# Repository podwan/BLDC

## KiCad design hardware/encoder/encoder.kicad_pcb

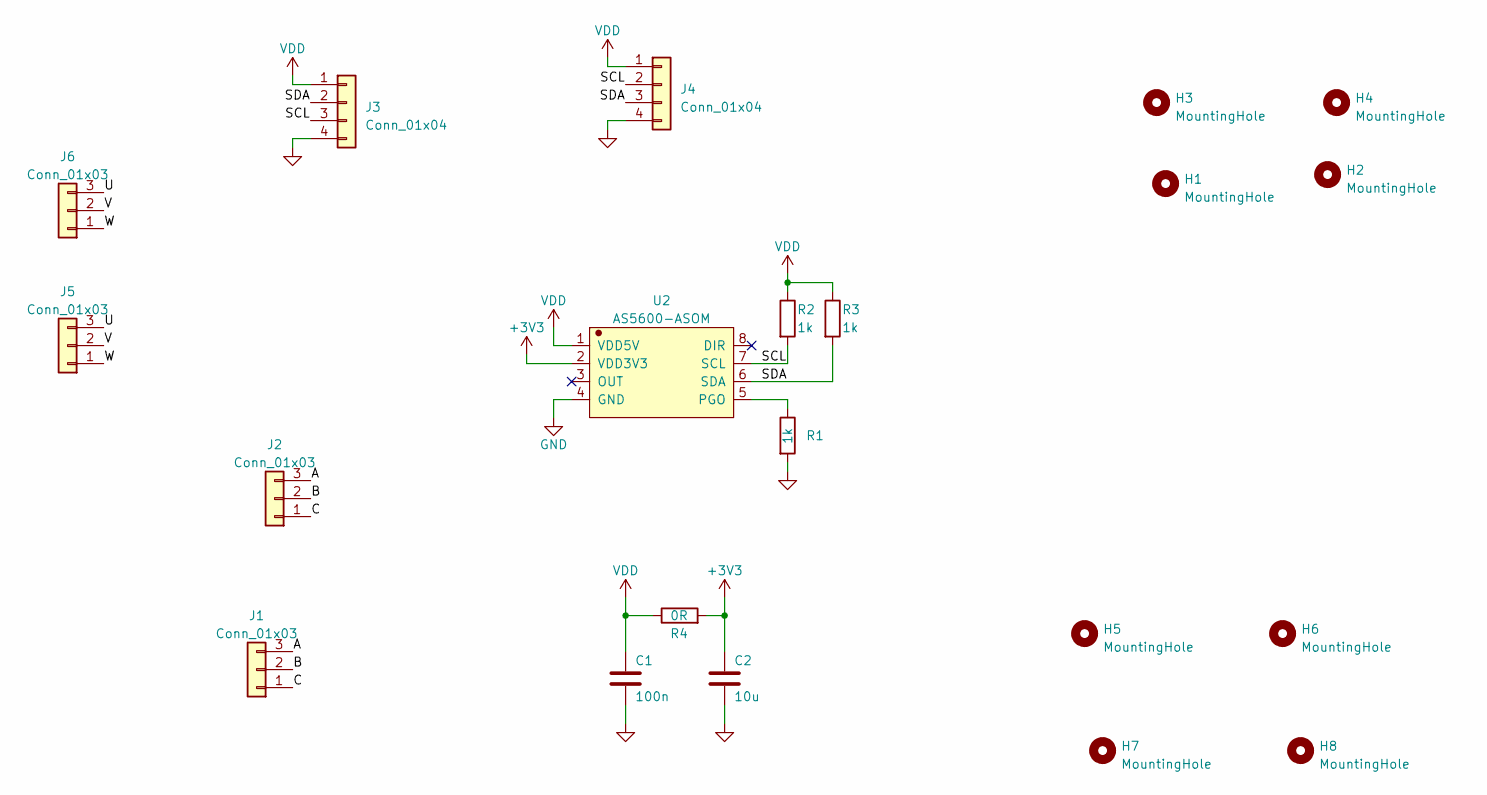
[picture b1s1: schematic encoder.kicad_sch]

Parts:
C1: 100n; C_0603_1608Metric_Pad1.08x0.95mm_HandSolder
C2: 10u; C_0805_2012Metric_Pad1.18x1.45mm_HandSolder
H1, H2, H3, H4: MountingHole; MountingHole_2.5mm_Pad_TopBottom
H5, H6, H7, H8: MountingHole; MountingHole_3mm_Pad_TopBottom
J1, J2: Conn_01x03; PinSocket_1x03_P2.54mm_Vertical
J3: Conn_01x04; PinSocket_1x04_P2.54mm_Vertical
J4: Conn_01x04; CONN-SMD_AFC10-S04QCA-00
J5, J6: Conn_01x03; CONN-SMD_AFC10-S03QCA-00
R1, R2, R3: 1k; C_0603_1608Metric_Pad1.08x0.95mm_HandSolder
R4: 0R; C_0603_1608Metric_Pad1.08x0.95mm_HandSolder
U2: AS5600-ASOM; SOIC-8_L5.0-W4.0-P1.27-LS6.0-BL

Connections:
+3V3: C2.1, R4.2, U2.2 (VDD3V3)
/A: J1.3, J2.3
/B: J1.2, J2.2
/C: J1.1, J2.1
/SCL: J3.3, J4.2, R2.2, U2.7 (SCL)
/SDA: J3.2, J4.3, R3.2, U2.6 (SDA)
/U: J5.3, J6.3
/V: J5.2, J6.2
/W: J5.1, J6.1
GND: C1.2, C2.2, J3.4, J4.4, R1.2, U2.4 (GND)
unnamed: R1.1, U2.5 (PGO)
VDD: C1.1, J3.1, J4.1, R2.1, R3.1, R4.1, U2.1 (VDD5V)

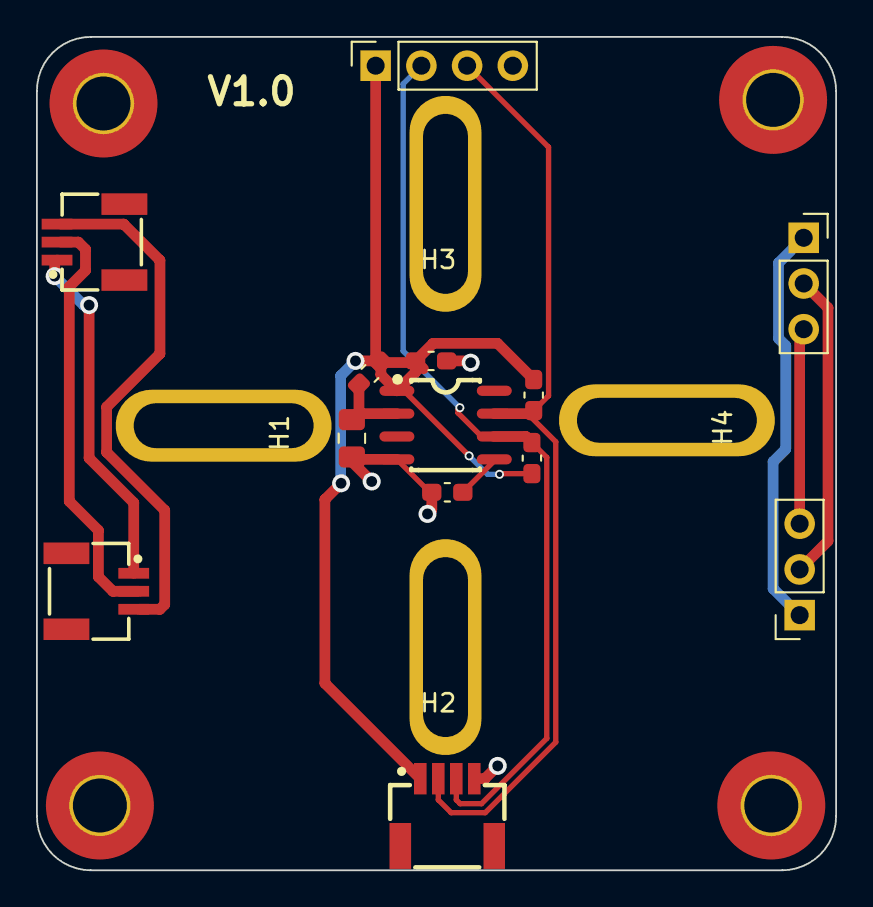
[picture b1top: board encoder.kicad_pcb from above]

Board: 2 copper layers, 44.4 x 46.3 mm, 21 parts (0 on the bottom side), 12 nets.

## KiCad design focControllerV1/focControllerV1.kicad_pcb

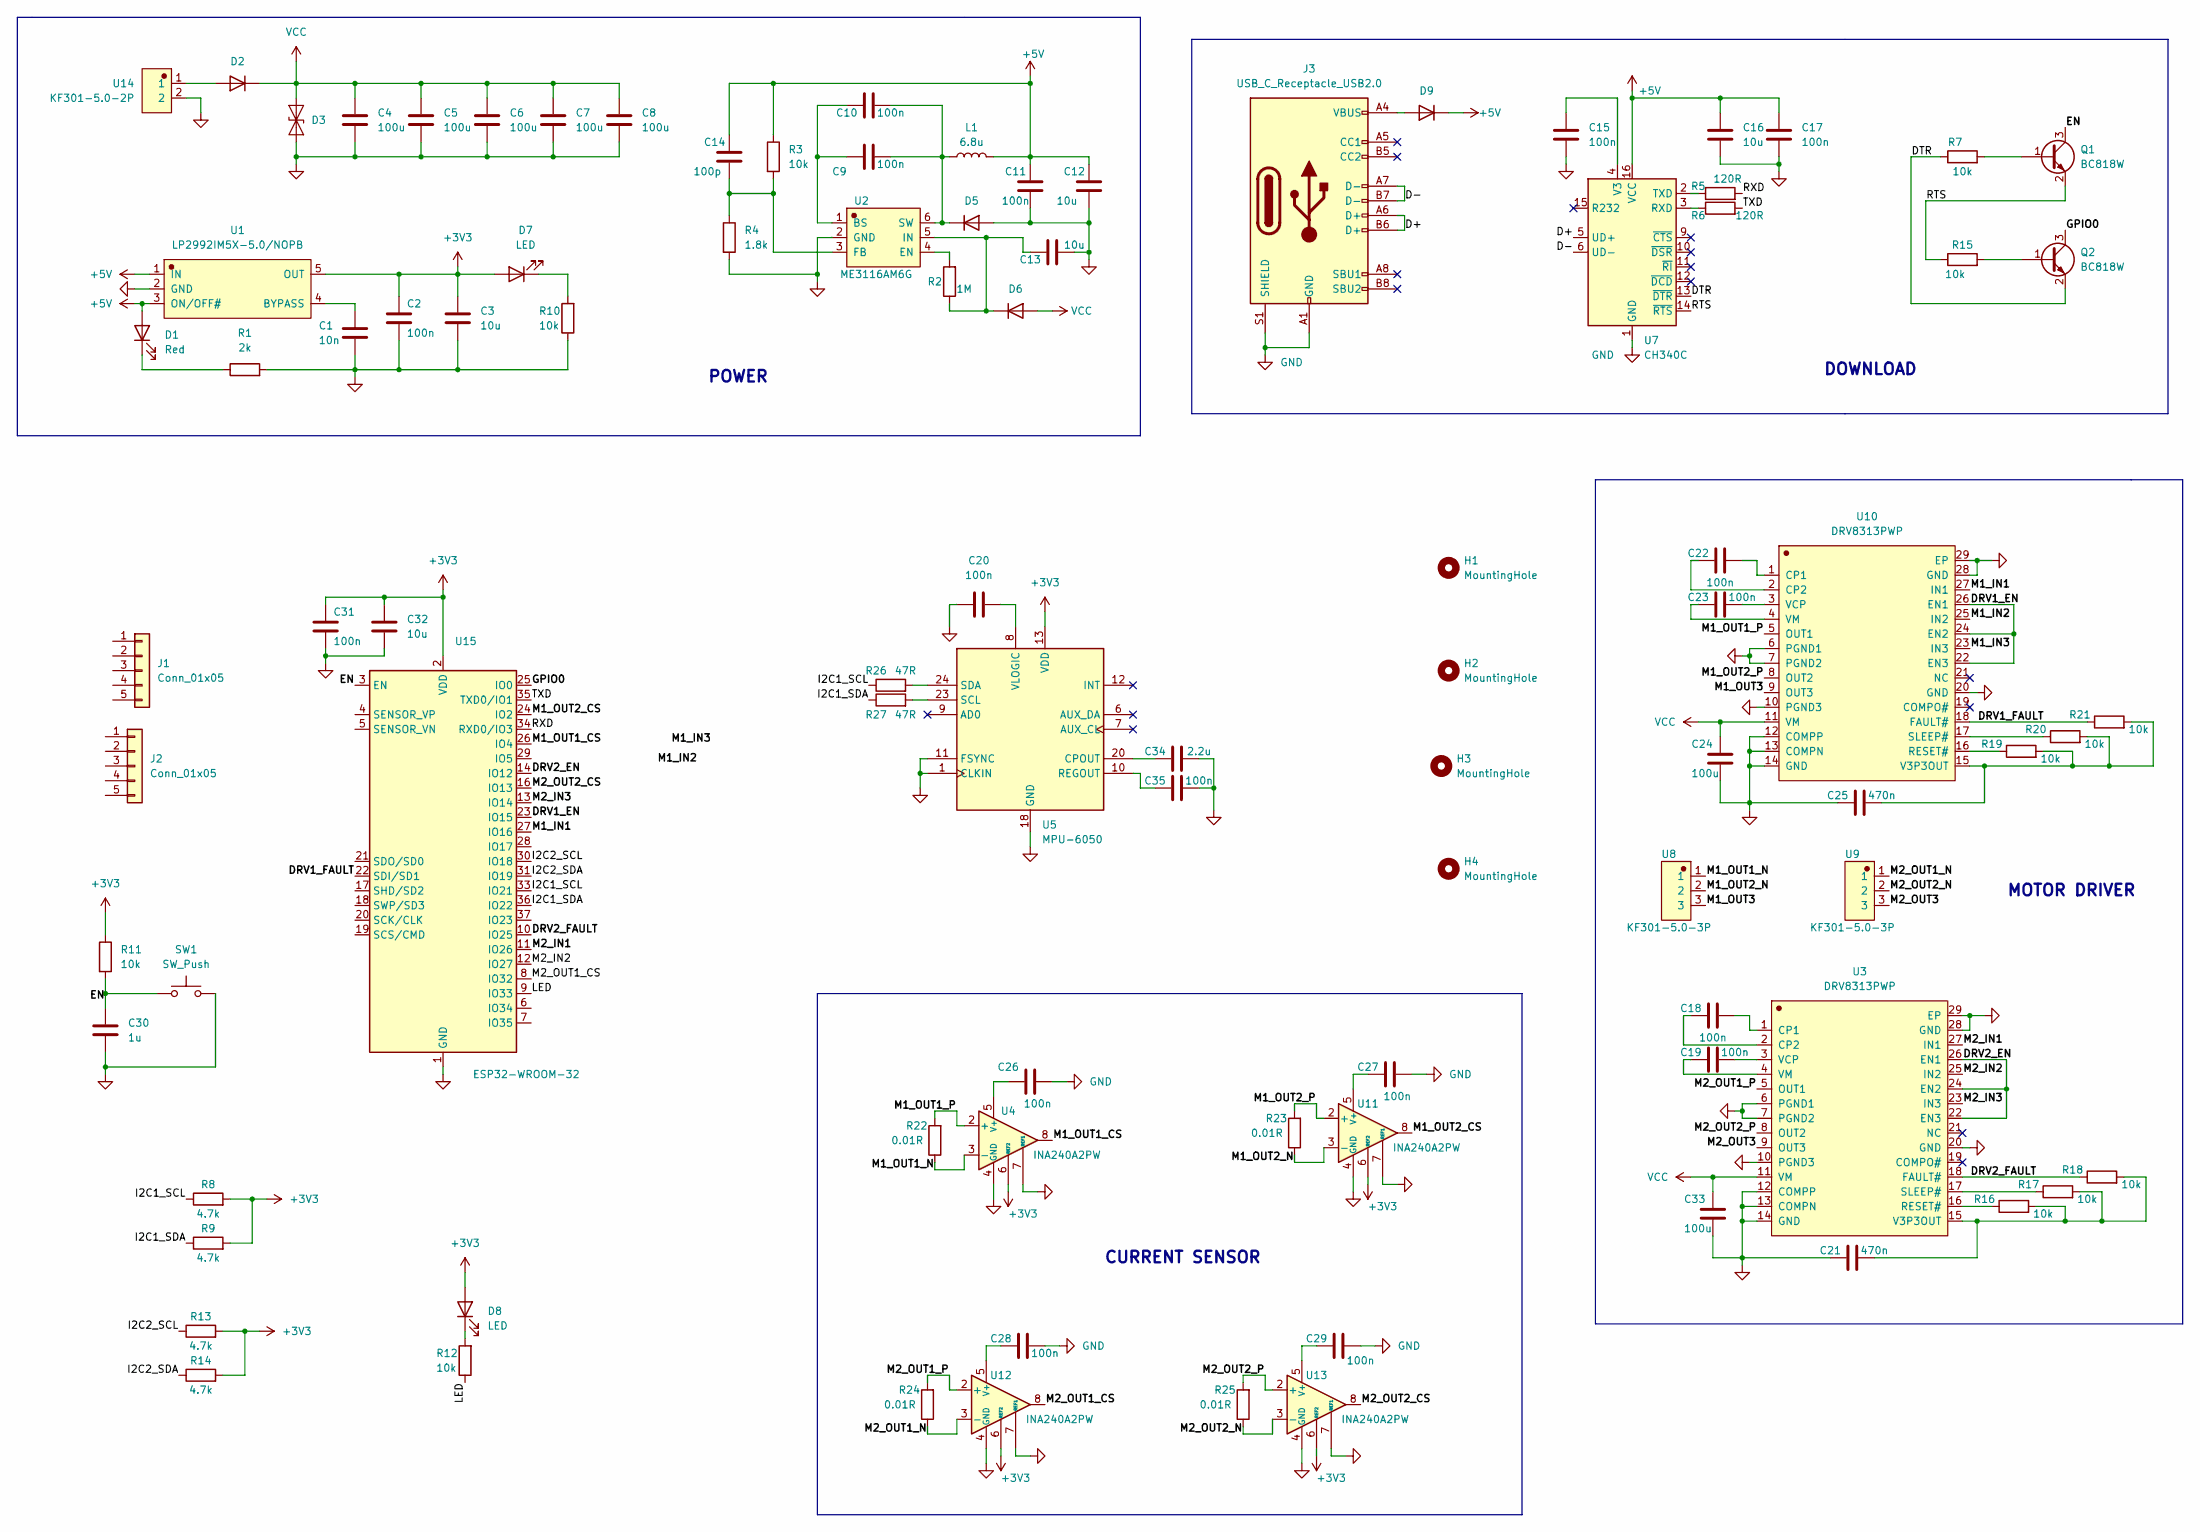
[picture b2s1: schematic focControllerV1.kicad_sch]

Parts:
C1: 10n; C_0603_1608Metric_Pad1.08x0.95mm_HandSolder
C2, C9, C10, C11, C15, C17, C18, C19, C20, C22, C23, C26, C27, C28, C29, C31, C35: 100n; C_0603_1608Metric_Pad1.08x0.95mm_HandSolder
C3, C12, C13, C16, C32: 10u; C_0603_1608Metric_Pad1.08x0.95mm_HandSolder
C4, C5, C6, C7, C8, C24, C33: 100u; C_1210_3225Metric_Pad1.33x2.70mm_HandSolder
C14: 100p; C_0603_1608Metric_Pad1.08x0.95mm_HandSolder
C21, C25: 470n; C_0603_1608Metric_Pad1.08x0.95mm_HandSolder
C30: 1u; C_0603_1608Metric_Pad1.08x0.95mm_HandSolder
C34: 2.2u; C_0603_1608Metric_Pad1.08x0.95mm_HandSolder
D1: Red; C_0603_1608Metric_Pad1.08x0.95mm_HandSolder
D2, D5, D6, D9: 1N4003; DO-214AC_L5.0-W2.5-LS5.0-FD
D3: SMAJ15CA; D_SMA
D7, D8: LED; C_0603_1608Metric_Pad1.08x0.95mm_HandSolder
H1, H2, H3, H4: MountingHole; MountingHole_2.2mm_M2_Pad
J1, J2: Conn_01x05; connector_5p
J3: USB_C_Receptacle_USB2.0; USB_C_Receptacle_G-Switch_GT-USB-7010ASV
L1: 6.8u; L_0805_2012Metric_Pad1.05x1.20mm_HandSolder
Q1, Q2: BC818W; SOT-323_SC-70
R1: 2k; C_0603_1608Metric_Pad1.08x0.95mm_HandSolder
R2: 1M; C_0603_1608Metric_Pad1.08x0.95mm_HandSolder
R3, R7, R10, R11, R12, R15, R16, R17, R18, R19, R20, R21: 10k; C_0603_1608Metric_Pad1.08x0.95mm_HandSolder
R4: 1.8k; C_0603_1608Metric_Pad1.08x0.95mm_HandSolder
R5, R6: 120R; C_0603_1608Metric_Pad1.08x0.95mm_HandSolder
R8, R9, R13, R14: 4.7k; C_0603_1608Metric_Pad1.08x0.95mm_HandSolder
R22, R23, R24, R25: 0.01R; R_1206_3216Metric_Pad1.30x1.75mm_HandSolder
R26, R27: 47R; C_0603_1608Metric_Pad1.08x0.95mm_HandSolder
SW1: SW_Push; SW_SPST_B3U-1000P
U1: LP2992IM5X-5.0/NOPB; SOT-23-5_L2.9-W1.6-P0.95-LS2.8-BR
U2: ME3116AM6G; SOT-23-6_L2.9-W1.6-P0.95-LS2.8-BL
U3, U10: DRV8313PWP; TSSOP-28_L9.7-W4.4-P0.65-LS6.4-TL-EP-2
U4, U11, U12, U13: INA240A2PW; TSSOP-8_4.4x3mm_P0.65mm
U5: MPU-6050; InvenSense_QFN-24_4x4mm_P0.5mm
U7: CH340C; SOIC-16_3.9x9.9mm_P1.27mm
U8, U9: KF301-5.0-3P; CONN-TH_3P-P5.00_KF301-5.0-3P
U14: KF301-5.0-2P; CONN-TH_P5.00_KF301-5.0-2P
U15: ESP32-WROOM-32

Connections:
+3V3: C2.1, C3.1, C31.1, C32.1, D7.2 (A), D8.2 (A), R8.2, R9.2, R11.1, R13.2, R14.2, U1.5 (OUT), U4.6 (REF2), U5.13 (VDD), U11.6 (REF2), U12.6 (REF2), U13.6 (REF2), U15.2 (VDD)
+5V: C11.2, C12.2, C14.1, C16.1, C17.1, D1.2 (A), D9.1 (K), L1.2, R3.1, U1.1 (IN), U1.3 (ON/OFF#), U7.16 (VCC)
/D+: J3.A6 (D+), J3.B6 (D+), U7.5 (UD+)
/D-: J3.A7 (D-), J3.B7 (D-), U7.6 (UD-)
/DRV1_EN: U10.22 (EN3), U10.24 (EN2), U10.26 (EN1), U15.23 (IO15)
/DRV1_FAULT: R21.1, U10.18 (FAULT#), U15.22 (SDI/SD1)
/DRV2_EN: U3.22 (EN3), U3.24 (EN2), U3.26 (EN1), U15.14 (IO12)
/DRV2_FAULT: R18.1, U3.18 (FAULT#), U15.10 (IO25)
/DTR: Q2.2 (E), R7.1, U7.13 (~DTR)
/EN: C30.1, Q1.3 (C), R11.2, SW1.1, U15.3 (EN)
/GPIO0: Q2.3 (C), U15.25 (IO0)
/I2C1_SCL: R8.1, R26.1, U15.33 (IO21)
/I2C1_SDA: R9.1, R27.1, U15.36 (IO22)
/I2C2_SCL: R13.1, U15.30 (IO18)
/I2C2_SDA: R14.1, U15.31 (IO19)
/LED: R12.1, U15.9 (IO33)
/M1_IN1: U10.27 (IN1), U15.27 (IO16)
/M1_OUT1_N: R22.1, U4.3 (-), U8.1
/M1_OUT1_P: R22.2, U4.2 (+), U10.5 (OUT1)
/M1_OUT2_N: R23.1, U8.2, U11.3 (-)
/M1_OUT2_P: R23.2, U10.8 (OUT2), U11.2 (+)
/M1_OUT3: U8.3, U10.9 (OUT3)
/M2_IN1: U3.27 (IN1), U15.11 (IO26)
/M2_IN2: U3.25 (IN2), U15.12 (IO27)
/M2_IN3: U3.23 (IN3), U15.13 (IO14)
/M2_OUT1_CS: U12.8, U15.8 (IO32)
/M2_OUT1_N: R24.1, U9.1, U12.3 (-)
/M2_OUT1_P: R24.2, U3.5 (OUT1), U12.2 (+)
/M2_OUT2_CS: U13.8, U15.16 (IO13)
/M2_OUT2_N: R25.1, U9.2, U13.3 (-)
/M2_OUT2_P: R25.2, U3.8 (OUT2), U13.2 (+)
/M2_OUT3: U3.9 (OUT3), U9.3
/RTS: Q1.2 (E), R15.1, U7.14 (~RTS)
/RXD: R5.2, U15.34 (RXD0/IO3)
/TXD: R6.2, U15.35 (TXD0/IO1)
GND: C1.2, C2.2, C3.2, C4.2, C5.2, C6.2, C7.2, C8.2, C11.1, C12.1, C13.1, C15.2, C16.2, C17.2, C20.1, C21.1, C24.2, C25.1, C26.2, C27.2, C28.2, C29.2, C30.2, C31.2, C32.2, C33.2, C34.1, C35.1, D3.1 (A1), D5.2 (A), J3.A1 (GND), J3.A12 (GND), J3.B1 (GND), J3.B12 (GND), J3.S1 (SHIELD), R1.2, R4.2, R10.1, SW1.2, U1.2 (GND), U2.2 (GND), U3.6 (PGND1), U3.7 (PGND2), U3.10 (PGND3), U3.12 (COMPP), U3.13 (COMPN), U3.14 (GND), U3.20 (GND), U3.28 (GND), U3.29 (EP), U4.1 (GND), U4.4 (GND), U4.7 (REF1), U5.1 (CLKIN), U5.11 (FSYNC), U5.18 (GND), U7.1 (GND), U10.6 (PGND1), U10.7 (PGND2), U10.10 (PGND3), U10.12 (COMPP), U10.13 (COMPN), U10.14 (GND), U10.20 (GND), U10.28 (GND), U10.29 (EP), U11.1 (GND), U11.4 (GND), U11.7 (REF1), U12.1 (GND), U12.4 (GND), U12.7 (REF1), U13.1 (GND), U13.4 (GND), U13.7 (REF1), U14.2, U15.1 (GND), U15.15 (GND), U15.38 (GND), U15.39 (GND)
unnamed: C19.1, U3.4 (VM)
unnamed: C23.1, U10.4 (VM)
unnamed: D1.1 (K), R1.1
unnamed: D2.2 (A), U14.1
unnamed: C9.2, C10.2, D5.1 (K), L1.1, U2.6 (SW)
unnamed: C13.2, D6.1 (K), R2.1, U2.5 (IN)
unnamed: D7.1 (K), R10.2
unnamed: D8.1 (K), R12.2
unnamed: D9.2 (A), J3.A4 (VBUS), J3.A9 (VBUS), J3.B4 (VBUS), J3.B9 (VBUS)
unnamed: Q1.1 (B), R7.2
unnamed: Q2.1 (B), R15.2
unnamed: C1.1, U1.4 (BYPASS)
unnamed: C9.1, C10.1, U2.1 (BS)
unnamed: R2.2, U2.4 (EN)
unnamed: C14.2, R3.2, R4.1, U2.3 (FB)
unnamed: C18.2, U3.1 (CP1)
unnamed: C18.1, U3.2 (CP2)
unnamed: R16.1, U3.16 (RESET#)
unnamed: R17.1, U3.17 (SLEEP#)
unnamed: C21.2, R16.2, R17.2, R18.2, U3.15 (V3P3OUT)
unnamed: C19.2, U3.3 (VCP)
unnamed: C26.1, U4.5 (V+)
unnamed: C34.2, U5.20 (CPOUT)
unnamed: C35.2, U5.10 (REGOUT)
unnamed: R27.2, U5.23 (SCL)
unnamed: R26.2, U5.24 (SDA)
unnamed: C20.2, U5.8 (VLOGIC)
unnamed: R6.1, U7.3 (RXD)
unnamed: R5.1, U7.2 (TXD)
unnamed: C15.1, U7.4 (V3)
unnamed: C22.2, U10.1 (CP1)
unnamed: C22.1, U10.2 (CP2)
unnamed: R19.1, U10.16 (RESET#)
unnamed: R20.1, U10.17 (SLEEP#)
unnamed: C25.2, R19.2, R20.2, R21.2, U10.15 (V3P3OUT)
unnamed: C23.2, U10.3 (VCP)
unnamed: C27.1, U11.5 (V+)
unnamed: C28.1, U12.5 (V+)
unnamed: C29.1, U13.5 (V+)
VCC: C4.1, C5.1, C6.1, C7.1, C8.1, C24.1, C33.1, D2.1 (K), D3.2 (A2), D6.2 (A), U3.11 (VM), U10.11 (VM)

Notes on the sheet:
DOWNLOAD
POWER
MOTOR DRIVER
CURRENT SENSOR

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
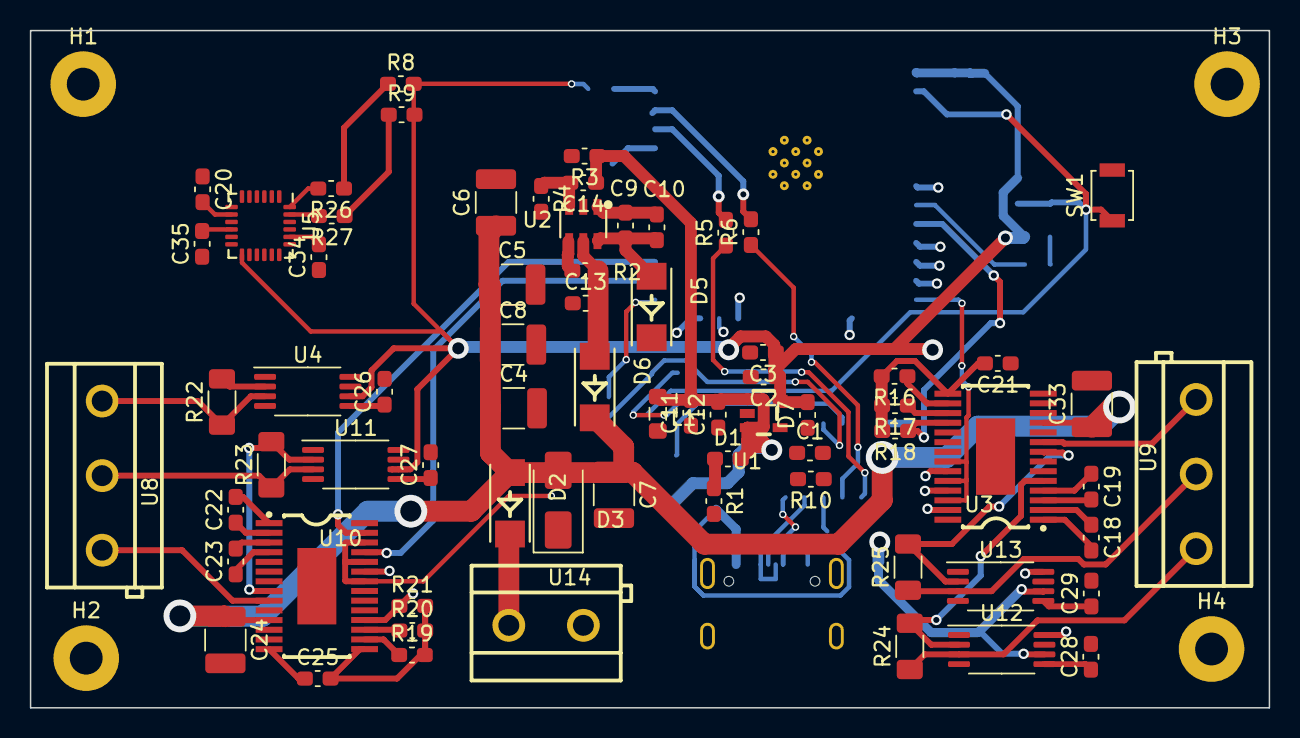
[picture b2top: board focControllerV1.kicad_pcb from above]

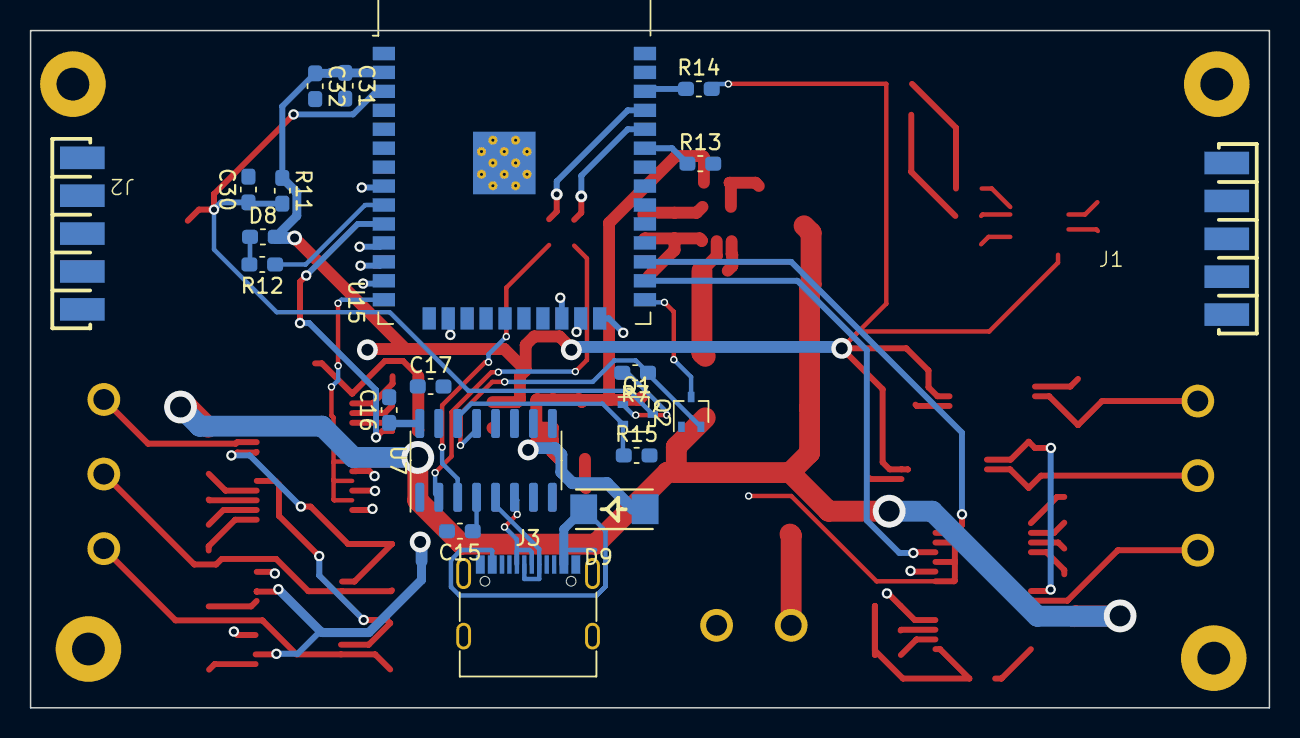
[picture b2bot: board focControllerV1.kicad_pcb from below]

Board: 4 copper layers, 83.1 x 45.4 mm, 95 parts (21 on the bottom side), 80 nets.

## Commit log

2023-07-25 725night
2023-07-26 原理图设计中
2023-07-27 准备布线
2023-12-17 add model and code
2023-12-18 准备测试波形
2023-12-24 通过上位机能观察到CCR值为马鞍波
2023-12-26 motor spin with current sensed
2023-12-26 open loop
2023-12-30 龙伯格观测器进行中
2023-12-31 theory update
2024-01-01 model update
2024-01-01 准备IF启动
2024-01-01 准备debug电流环
2024-01-06 encoder board added
2024-01-06 open loop done
2024-01-07 无感闭环中
2024-01-09 更新无感观测器theory
2024-01-10 准备速度环代码
2024-01-11 霍尔闭环中
2024-01-12 开环霍尔测速不对应
2024-01-13 准备交换代码测试霍尔测速
2024-01-23 “完成as5600驱动及电机手柄模型”
2024-01-24 准备加入串口指令控制位置闭环
2024-01-26 准备加入指令解析
2024-01-28 继续参照完善代码
2024-01-29 速度开环未完待续
2024-01-31 移植freeRTOS中
2024-01-31 freeRTOS移植结束
2024-02-03 完成串口
2024-02-03 C++混编
2024-02-04 c++混编中
2024-02-04 c++混编结尾中
2024-02-06 需继续完善速度闭环
2024-02-07 debug openloop
2024-02-20 try CUBEIDE
